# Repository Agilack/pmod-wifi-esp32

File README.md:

PMOD Wifi ESP32
===============

This project is a PMOD module that allow to add a wireless wifi interface to a
project.

CAD source
----------

This board has been designed using KiCad EDA (version 5). All sources files
(schematics, routing, ...) are available into the `prj-kicad` folder. You can
re-use this design under terms of the Creative Commons ShareAlike license
(CC BY-SA)

<table>
<tr>
<td></td>
<td></td>
</tr>
<tr>
<td>Fig1: Preview of the KiCad schematics</td>
<td>Fig2: Preview of the KiCad routing</td>
</tr>
</table>

Previous version (rev1)
-----------------------

A major hardware bug into external flash memory routing have been found into
previous version. The rev1 must be considered unusable. More informations
about this bug is available into history (see tag `rev1`)

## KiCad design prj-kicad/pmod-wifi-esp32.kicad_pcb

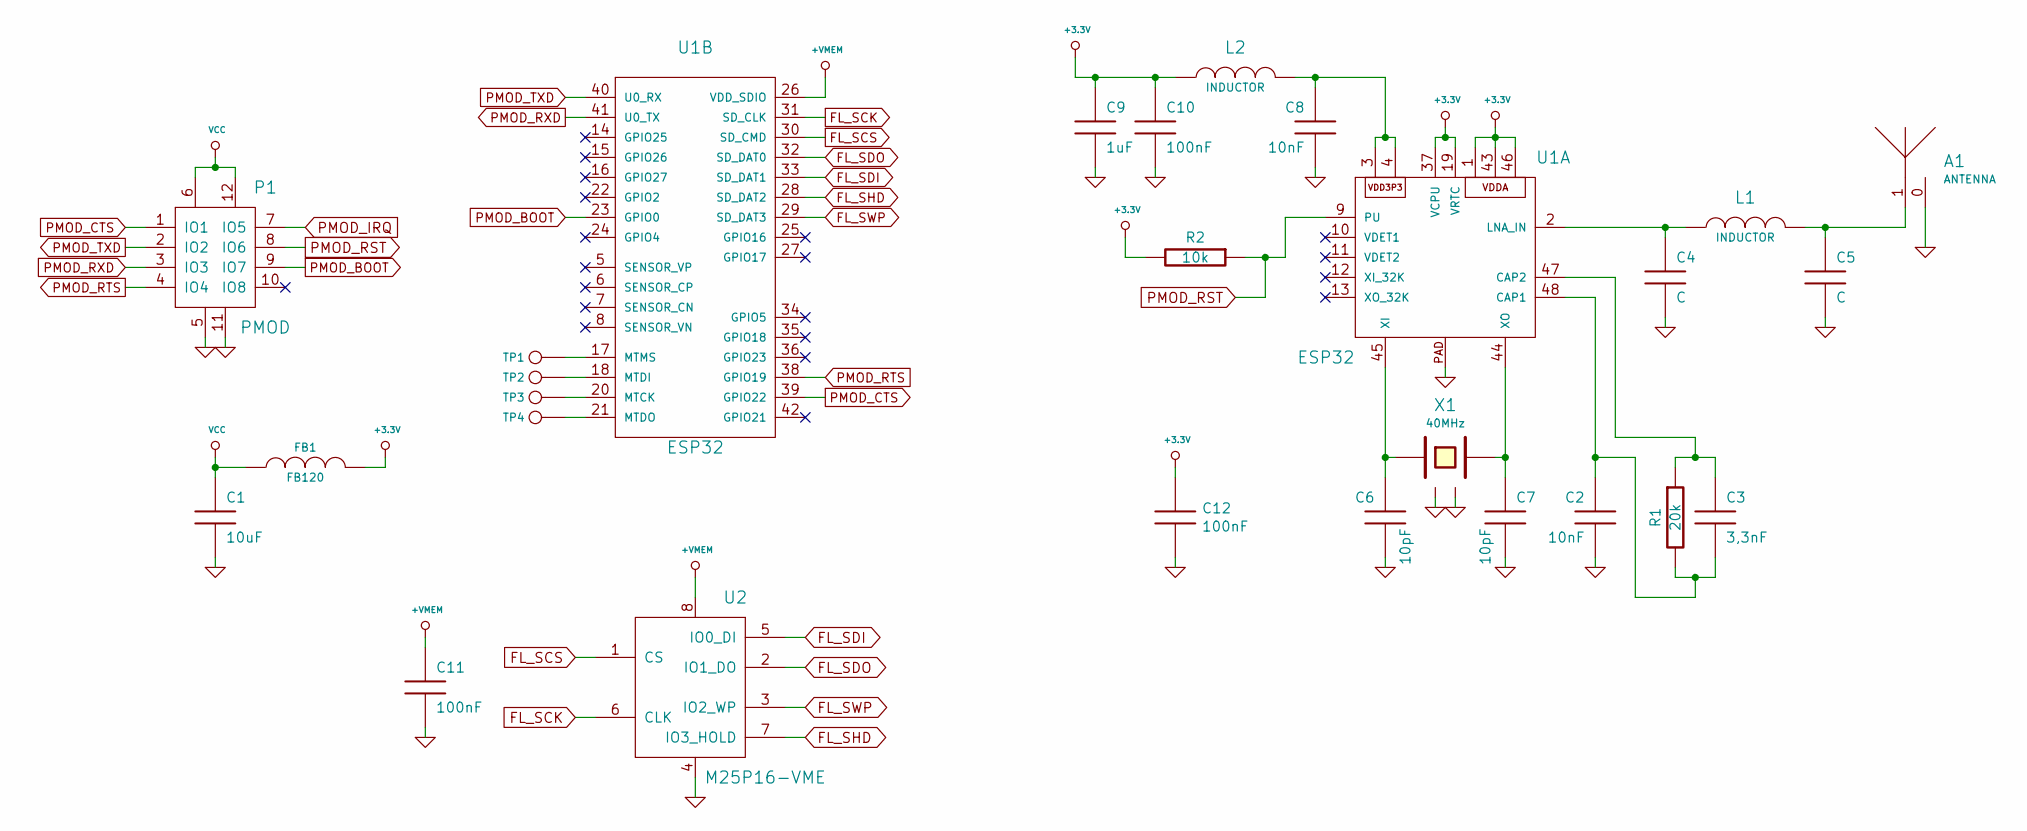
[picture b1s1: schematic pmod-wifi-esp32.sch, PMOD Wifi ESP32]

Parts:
A1: ANTENNA; ANT_7488910245
C1: 10uF; SMD0805
C2, C8: 10nF; SMD0603
C3: 3,3nF; SMD0603
C4, C5: C; SMD0603
C6, C7: 10pF; SMD0603
C9: 1uF; SMD0603
C10, C11, C12: 100nF; SMD0603
FB1: FB120; SMD0603
L1, L2: INDUCTOR; SMD0603
P1: PMOD; CONN_PMOD-Male
R1: 20k; SMD0603
R2: 10k; SMD0603
TP1, TP2, TP3, TP4: CONN_1; TP_SMD
U1: ESP32; QFN48-04
U2: M25P16-VME; SOIC-8
X1: 40MHz; Q_3.2x2.5

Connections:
+3.3V: C9.1, C10.1, C12.1, FB1.2, L2.1, R2.2, U1.1, U1.19 (VRTC), U1.37 (VCPU), U1.43, U1.46
+VMEM: C11.1, U1.26 (VDD_SDIO), U2.8
FL_SCK: U1.31 (SD_CLK), U2.6 (CLK)
FL_SCS: U1.30 (SD_CMD), U2.1 (CS)
FL_SDI: U1.33 (SD_DAT1), U2.5 (IO0_DI)
FL_SDO: U1.32 (SD_DAT0), U2.2 (IO1_DO)
FL_SHD: U1.28 (SD_DAT2), U2.7 (IO3_HOLD)
FL_SWP: U1.29 (SD_DAT3), U2.3 (IO2_WP)
GND: A1.0, C1.2, C2.2, C4.2, C5.2, C6.2, C7.2, C8.2, C9.2, C10.2, C11.2, C12.2, P1.5, P1.11, U1.PAD, U2.4, X1.2, X1.4
unnamed: A1.1, C5.1, L1.2
unnamed: C2.1, C3.2, R1.2, U1.48 (CAP1)
unnamed: C3.1, R1.1, U1.47 (CAP2)
unnamed: C4.1, L1.1, U1.2 (LNA_IN)
unnamed: C6.1, U1.45 (XI), X1.3
unnamed: C7.1, U1.44 (XO), X1.1
unnamed: C8.1, L2.2, U1.3, U1.4
unnamed: TP1.1, U1.17 (MTMS)
unnamed: TP2.1, U1.18 (MTDI)
unnamed: TP3.1, U1.20 (MTCK)
unnamed: TP4.1, U1.21 (MTDO)
PMOD_BOOT: P1.9 (IO7), U1.23 (GPIO0)
PMOD_CTS: P1.1 (IO1), U1.39 (GPIO22)
PMOD_IRQ: P1.7 (IO5)
PMOD_RST: P1.8 (IO6), R2.1, U1.9 (PU)
PMOD_RTS: P1.4 (IO4), U1.38 (GPIO19)
PMOD_RXD: P1.3 (IO3), U1.41 (U0_TX)
PMOD_TXD: P1.2 (IO2), U1.40 (U0_RX)
VCC: C1.1, FB1.1, P1.6, P1.12

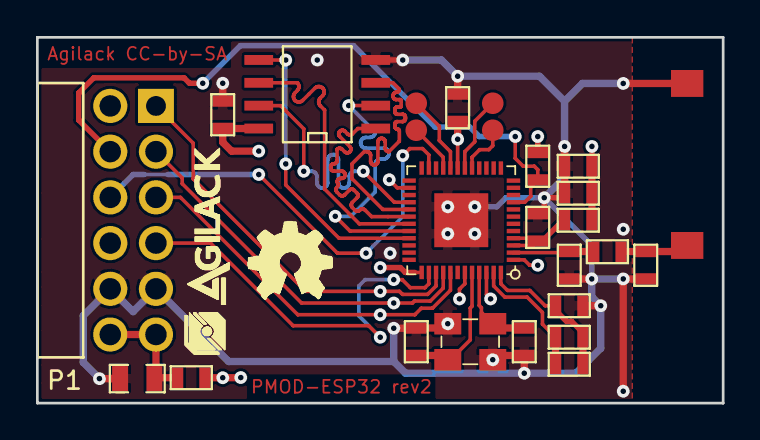
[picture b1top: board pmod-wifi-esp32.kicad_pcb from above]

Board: 4 copper layers, 38.1 x 20.3 mm, 28 parts (0 on the bottom side), 27 nets.

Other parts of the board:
agilack-11.5: 450px; logo-agilack-11.5
ohw_logo: VAL**; logo-ohw

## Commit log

2020-07-20 = Create kicad project and draw schematics
2020-07-21 = ADD: PCB routing
2020-07-21 = ADD: Generate production files
2020-08-01 = ADD: Insert picture of the PCB rev1. Add note about major hardware bug
2020-08-28 = UPD: Fix bug of flash memory ios ; add a signal to control "boot" pin from pmod
2020-08-29 = ADD: Generate production files for rev2

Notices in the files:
prj-kicad/pmod-wifi-esp32.kicad_pcb:
License: CC-by-SA 2.0
Agilack CC-by-SA
